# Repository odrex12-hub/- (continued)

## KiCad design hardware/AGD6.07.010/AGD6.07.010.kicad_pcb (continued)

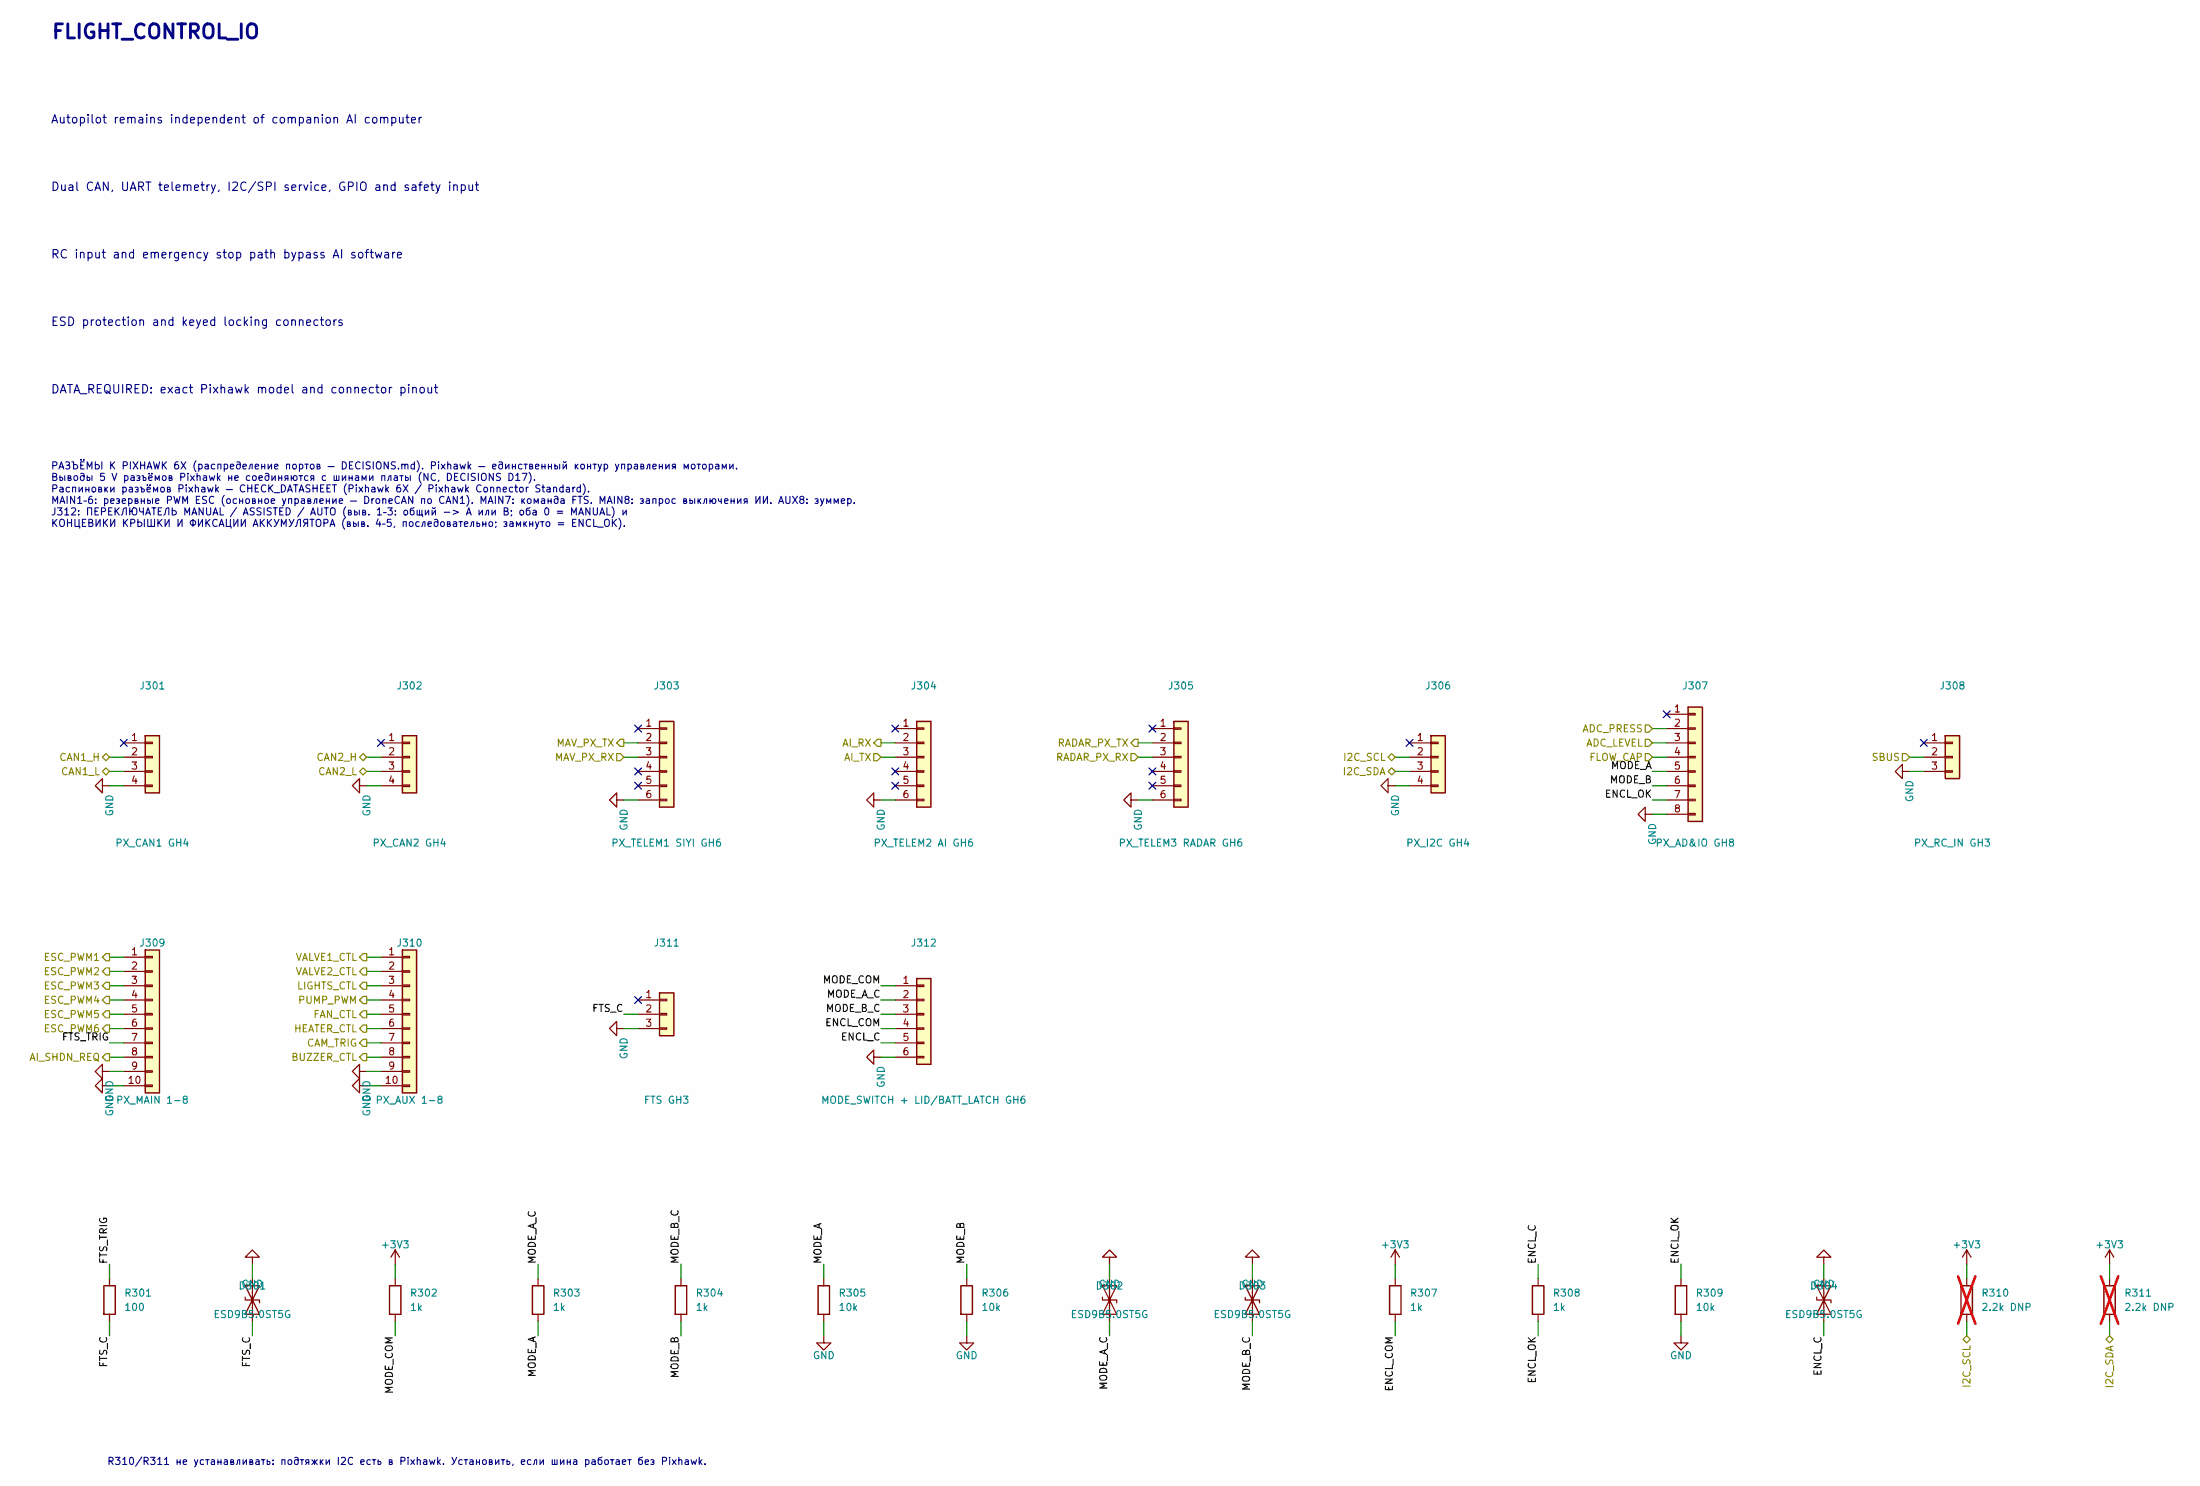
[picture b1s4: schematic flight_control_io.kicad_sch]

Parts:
D301, D302, D303, D304: ESD9B5.0ST5G; D_SOD-923
J301: PX_CAN1 GH4; JST_GH_SM04B-GHS-TB_1x04-1MP_P1.25mm_Horizontal
J302: PX_CAN2 GH4; JST_GH_SM04B-GHS-TB_1x04-1MP_P1.25mm_Horizontal
J303: PX_TELEM1 SIYI GH6; JST_GH_SM06B-GHS-TB_1x06-1MP_P1.25mm_Horizontal
J304: PX_TELEM2 AI GH6; JST_GH_SM06B-GHS-TB_1x06-1MP_P1.25mm_Horizontal
J305: PX_TELEM3 RADAR GH6; JST_GH_SM06B-GHS-TB_1x06-1MP_P1.25mm_Horizontal
J306: PX_I2C GH4; JST_GH_SM04B-GHS-TB_1x04-1MP_P1.25mm_Horizontal
J307: PX_AD&IO GH8; JST_GH_SM08B-GHS-TB_1x08-1MP_P1.25mm_Horizontal
J308: PX_RC_IN GH3; JST_GH_SM03B-GHS-TB_1x03-1MP_P1.25mm_Horizontal
J309: PX_MAIN 1-8; PinHeader_1x10_P2.54mm_Vertical
J310: PX_AUX 1-8; PinHeader_1x10_P2.54mm_Vertical
J311: FTS GH3; JST_GH_SM03B-GHS-TB_1x03-1MP_P1.25mm_Horizontal
J312: MODE_SWITCH + LID/BATT_LATCH GH6; JST_GH_SM06B-GHS-TB_1x06-1MP_P1.25mm_Horizontal
R301: 100; R_0402_1005Metric
R302, R303, R304, R307, R308: 1k; R_0402_1005Metric
R305, R306, R309: 10k; R_0402_1005Metric
R310, R311: 2.2k DNP; R_0402_1005Metric; not fitted

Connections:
+3V3: R302.1, R307.1, R310.1, R311.1; also elsewhere on the board
/ADC_LEVEL: J307.3; also elsewhere on the board
/ADC_PRESS: J307.2; also elsewhere on the board
/AI_RX: J304.2; also elsewhere on the board
/AI_SHDN_REQ: J309.8; also elsewhere on the board
/AI_TX: J304.3; also elsewhere on the board
/BUZZER_CTL: J310.8; also elsewhere on the board
/CAM_TRIG: J310.7; also elsewhere on the board
/CAN1_H: J301.2; also elsewhere on the board
/CAN1_L: J301.3; also elsewhere on the board
/CAN2_H: J302.2; also elsewhere on the board
/CAN2_L: J302.3; also elsewhere on the board
/ESC_PWM1: J309.1; also elsewhere on the board
/ESC_PWM2: J309.2; also elsewhere on the board
/ESC_PWM3: J309.3; also elsewhere on the board
/ESC_PWM4: J309.4; also elsewhere on the board
/ESC_PWM5: J309.5; also elsewhere on the board
/ESC_PWM6: J309.6; also elsewhere on the board
/FAN_CTL: J310.5; also elsewhere on the board
/FLIGHT_CONTROL_IO/ENCL_C: D304.1 (A1), J312.5, R308.1
/FLIGHT_CONTROL_IO/ENCL_COM: J312.4, R307.2
/FLIGHT_CONTROL_IO/ENCL_OK: J307.7, R308.2, R309.1
/FLIGHT_CONTROL_IO/FTS_C: D301.1 (A1), J311.2, R301.2
/FLIGHT_CONTROL_IO/FTS_TRIG: J309.7, R301.1
/FLIGHT_CONTROL_IO/MODE_A: J307.5, R303.2, R305.1
/FLIGHT_CONTROL_IO/MODE_A_C: D302.1 (A1), J312.2, R303.1
/FLIGHT_CONTROL_IO/MODE_B: J307.6, R304.2, R306.1
/FLIGHT_CONTROL_IO/MODE_B_C: D303.1 (A1), J312.3, R304.1
/FLIGHT_CONTROL_IO/MODE_COM: J312.1, R302.2
/FLOW_CAP: J307.4; also elsewhere on the board
/HEATER_CTL: J310.6; also elsewhere on the board
/I2C_SCL: J306.2, R310.2; also elsewhere on the board
/I2C_SDA: J306.3, R311.2; also elsewhere on the board
/LIGHTS_CTL: J310.3; also elsewhere on the board
/MAV_PX_RX: J303.3; also elsewhere on the board
/MAV_PX_TX: J303.2; also elsewhere on the board
/PUMP_PWM: J310.4; also elsewhere on the board
/RADAR_PX_RX: J305.3; also elsewhere on the board
/RADAR_PX_TX: J305.2; also elsewhere on the board
/SBUS: J308.2; also elsewhere on the board
/VALVE1_CTL: J310.1; also elsewhere on the board
/VALVE2_CTL: J310.2; also elsewhere on the board
GND: D301.2 (A2), D302.2 (A2), D303.2 (A2), D304.2 (A2), J301.4, J302.4, J303.6, J304.6, J305.6, J306.4, J307.8, J308.3, J309.9, J309.10, J310.9, J310.10, J311.3, J312.6, R305.2, R306.2, R309.2; also elsewhere on the board

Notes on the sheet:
RC input and emergency stop path bypass AI software
Dual CAN, UART telemetry, I2C/SPI service, GPIO and safety input
Autopilot remains independent of companion AI computer
FLIGHT_CONTROL_IO
DATA_REQUIRED: exact Pixhawk model and connector pinout
ESD protection and keyed locking connectors
РАЗЪЁМЫ К PIXHAWK 6X (распределение портов — DECISIONS.md). Pixhawk — единственный контур управления моторами. Выводы 5 V разъёмов Pixhawk не соединяются с шинами платы (NC, DECISIONS D17). Распиновки разъёмов Pixhawk — CHECK_DATASHEET (Pixhawk 6X / Pixhawk Connector Standard). MAIN1–6: резервные P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
R310/R311 не устанавливать: подтяжки I2C есть в Pixhawk. Установить, если шина работает без Pixhawk.

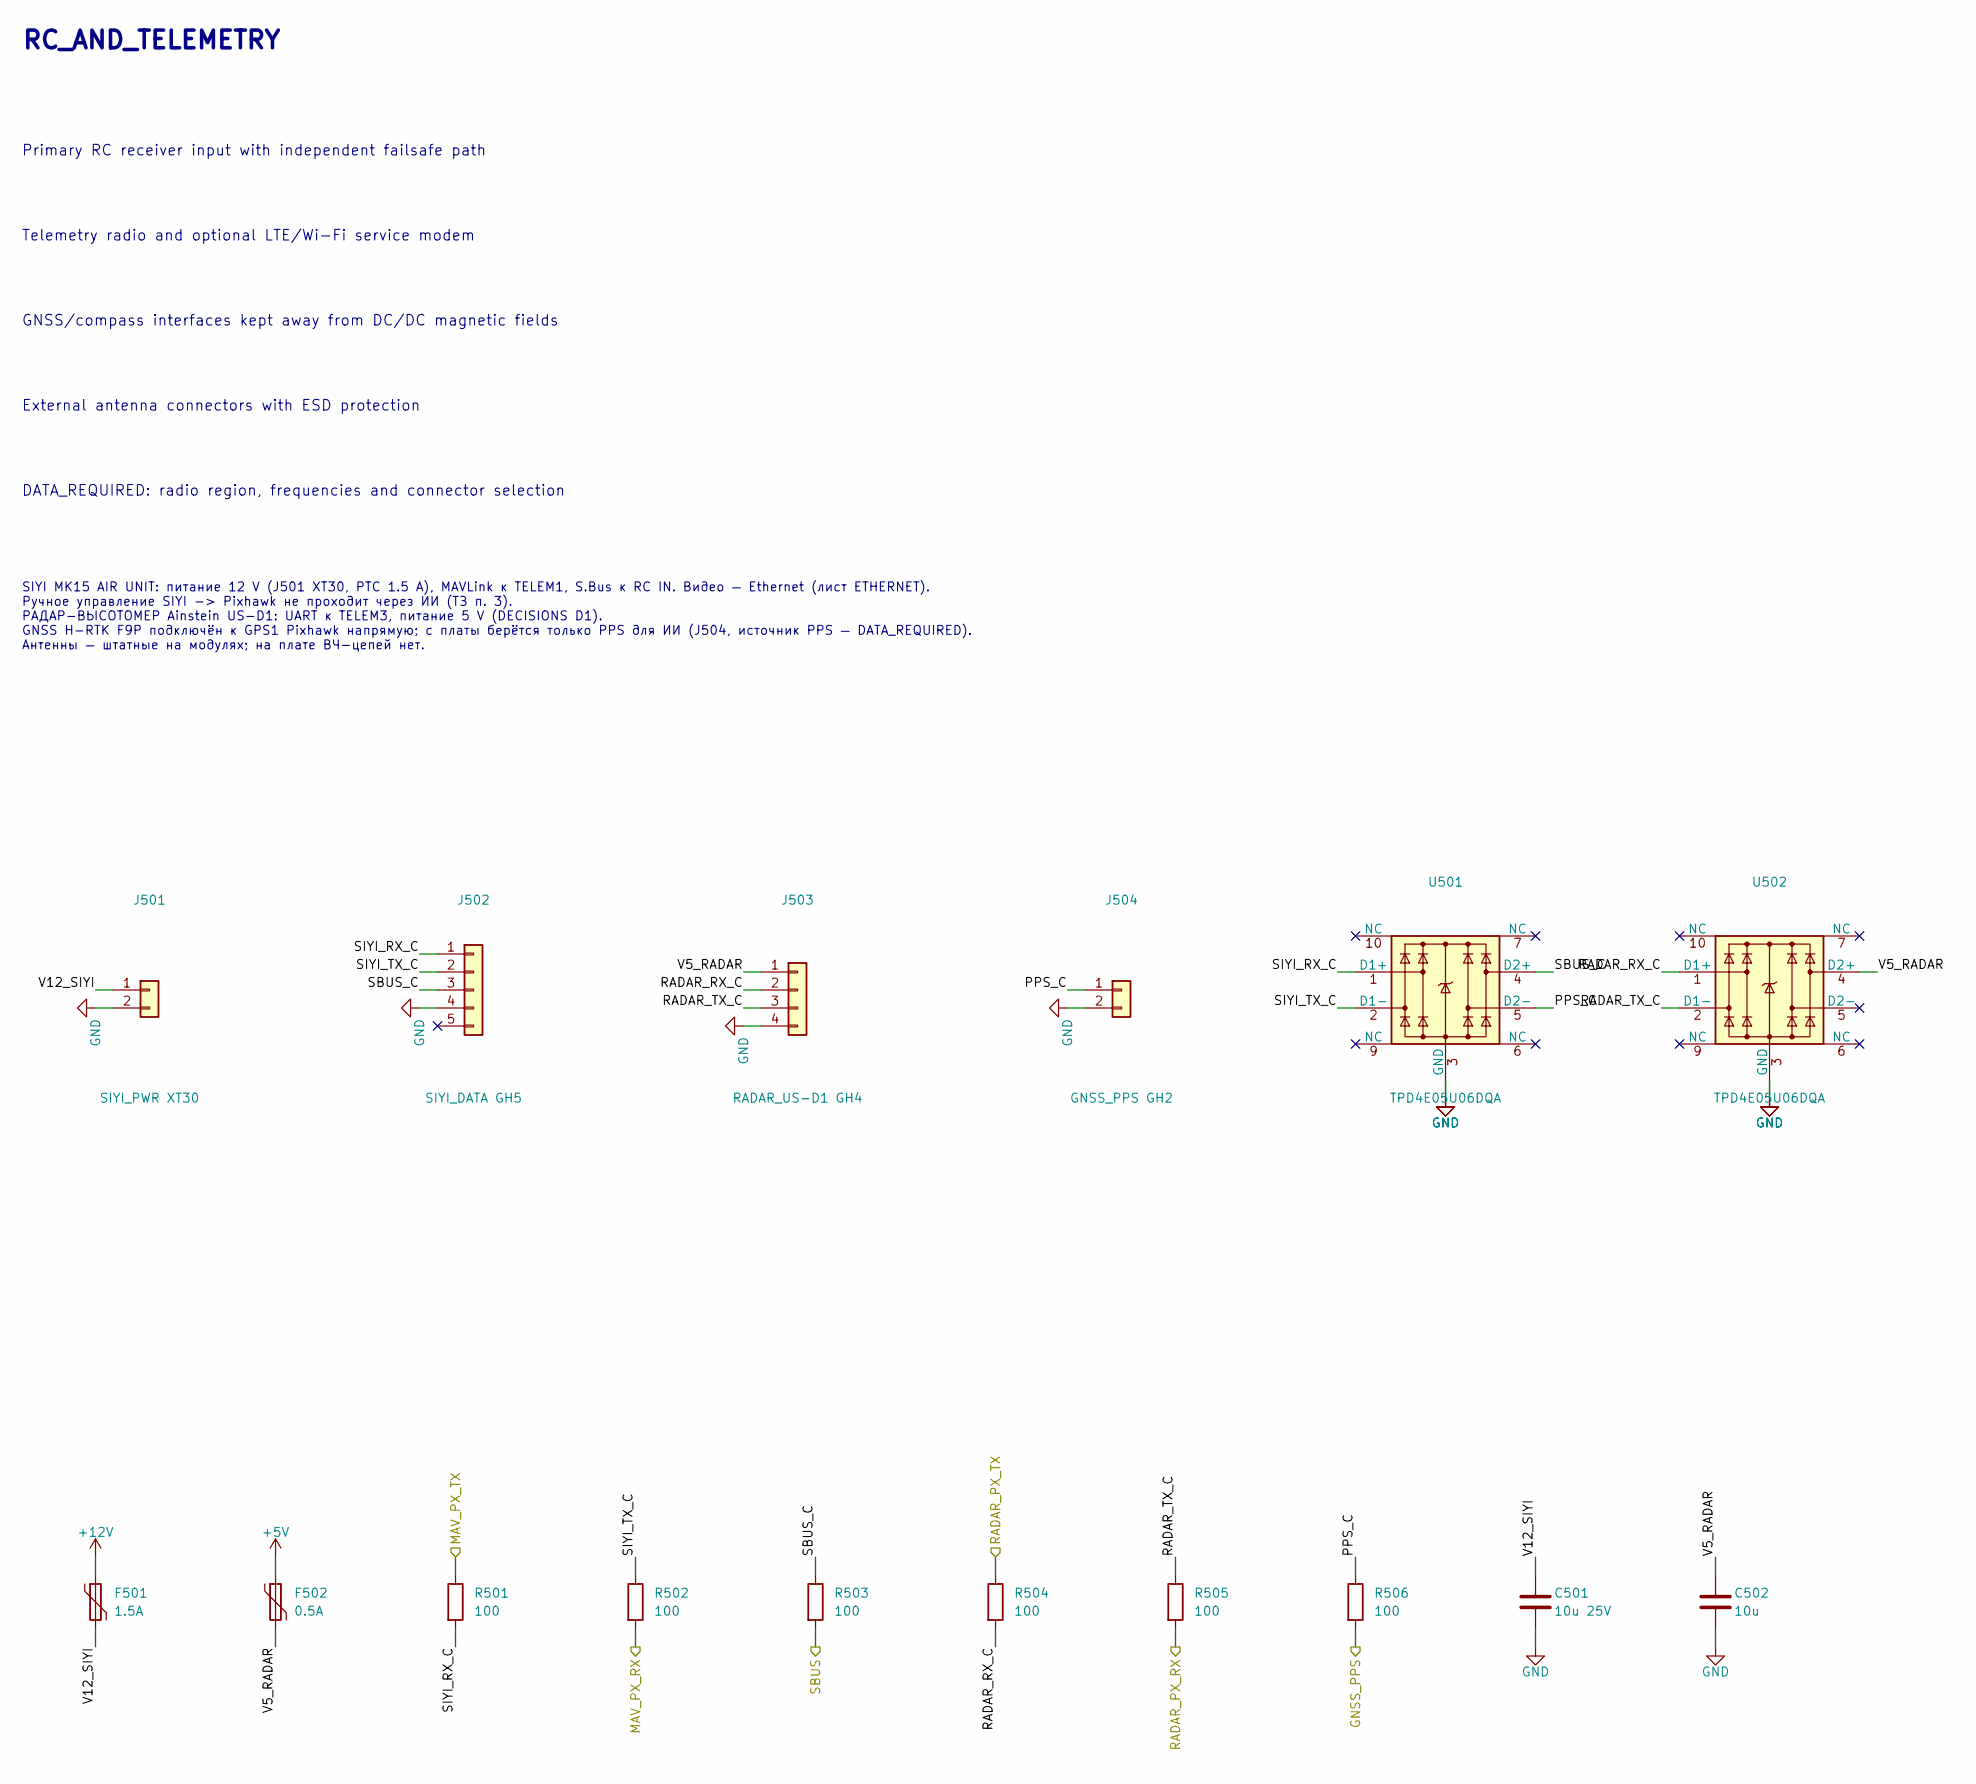
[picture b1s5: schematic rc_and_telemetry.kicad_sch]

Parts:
C501: 10u 25V; C_1210_3225Metric
C502: 10u; C_0805_2012Metric
F501: 1.5A; Fuse_1812_4532Metric
F502: 0.5A; Fuse_1206_3216Metric
J501: SIYI_PWR XT30; AMASS_XT30PW-F_1x02_P2.50mm_Horizontal
J502: SIYI_DATA GH5; JST_GH_SM05B-GHS-TB_1x05-1MP_P1.25mm_Horizontal
J503: RADAR_US-D1 GH4; JST_GH_SM04B-GHS-TB_1x04-1MP_P1.25mm_Horizontal
J504: GNSS_PPS GH2; JST_GH_SM02B-GHS-TB_1x02-1MP_P1.25mm_Horizontal
R501, R502, R503, R504, R505, R506: 100; R_0402_1005Metric
U501, U502: TPD4E05U06DQA; USON-10_2.5x1.0mm_P0.5mm

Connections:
+5V: F502.1; also elsewhere on the board
+12V: F501.1; also elsewhere on the board
/GNSS_PPS: R506.2; also elsewhere on the board
/MAV_PX_RX: R502.2; also elsewhere on the board
/MAV_PX_TX: R501.1; also elsewhere on the board
/RADAR_PX_RX: R505.2; also elsewhere on the board
/RADAR_PX_TX: R504.1; also elsewhere on the board
/RC_AND_TELEMETRY/PPS_C: J504.1, R506.1, U501.5 (D2-)
/RC_AND_TELEMETRY/RADAR_RX_C: J503.2, R504.2, U502.1 (D1+)
/RC_AND_TELEMETRY/RADAR_TX_C: J503.3, R505.1, U502.2 (D1-)
/RC_AND_TELEMETRY/SBUS_C: J502.3, R503.1, U501.4 (D2+)
/RC_AND_TELEMETRY/SIYI_RX_C: J502.1, R501.2, U501.1 (D1+)
/RC_AND_TELEMETRY/SIYI_TX_C: J502.2, R502.1, U501.2 (D1-)
/RC_AND_TELEMETRY/V5_RADAR: C502.1, F502.2, J503.1, U502.4 (D2+)
/RC_AND_TELEMETRY/V12_SIYI: C501.1, F501.2, J501.1
/SBUS: R503.2; also elsewhere on the board
GND: C501.2, C502.2, J501.2, J502.4, J503.4, J504.2, U501.3 (GND), U501.8 (GND), U502.3 (GND), U502.8 (GND); also elsewhere on the board

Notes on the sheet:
DATA_REQUIRED: radio region, frequencies and connector selection
Primary RC receiver input with independent failsafe path
GNSS/compass interfaces kept away from DC/DC magnetic fields
Telemetry radio and optional LTE/Wi-Fi service modem
RC_AND_TELEMETRY
External antenna connectors with ESD protection
SIYI MK15 AIR UNIT: питание 12 V (J501 XT30, PTC 1.5 A), MAVLink к TELEM1, S.Bus к RC IN. Видео — Ethernet (лист ETHERNET). Ручное управление SIYI -> Pixhawk не проходит через ИИ (ТЗ п. 3). РАДАР-ВЫСОТОМЕР Ainstein US-D1: UART к TELEM3, питание 5 V (DECISIONS D1). GNSS H-RTK F9P подключён к GPS1 Pi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

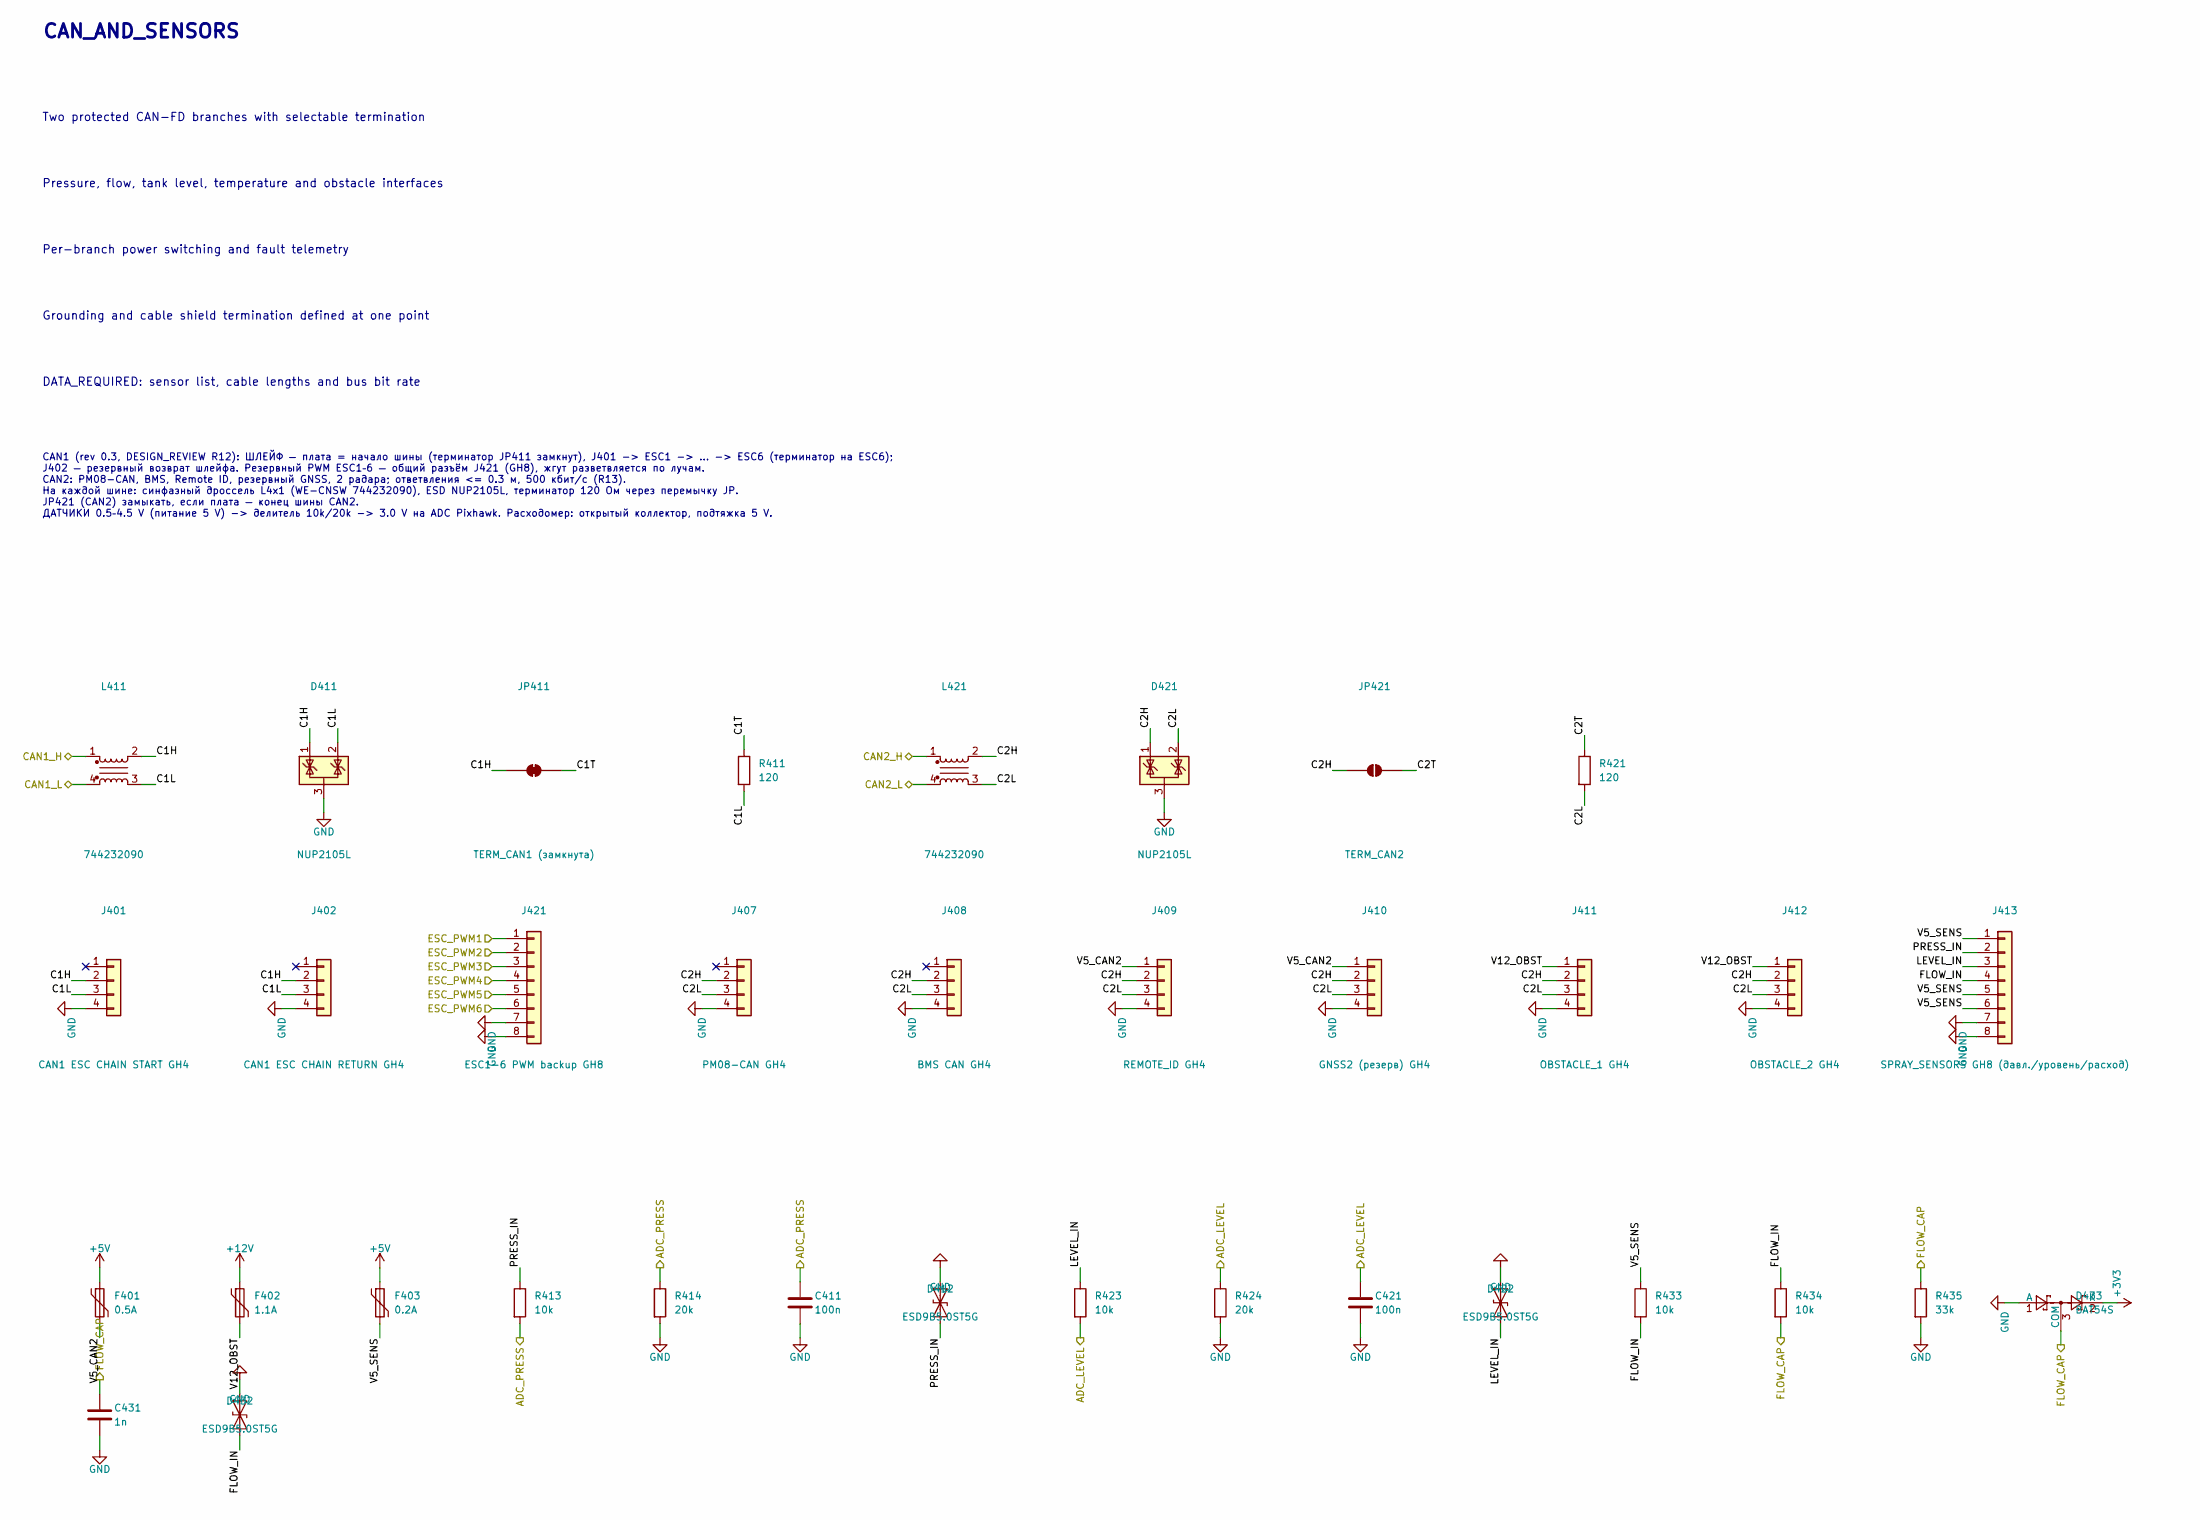
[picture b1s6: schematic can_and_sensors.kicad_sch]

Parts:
C411, C421: 100n; C_0402_1005Metric
C431: 1n; C_0402_1005Metric
D411, D421: NUP2105L; SOT-23
D412, D422, D432: ESD9B5.0ST5G; D_SOD-923
D433: BAT54S; SOT-23
F401: 0.5A; Fuse_1206_3216Metric
F402: 1.1A; Fuse_1812_4532Metric
F403: 0.2A; Fuse_1206_3216Metric
J401: CAN1 ESC CHAIN START GH4; JST_GH_SM04B-GHS-TB_1x04-1MP_P1.25mm_Horizontal
J402: CAN1 ESC CHAIN RETURN GH4; JST_GH_SM04B-GHS-TB_1x04-1MP_P1.25mm_Horizontal
J407: PM08-CAN GH4; JST_GH_SM04B-GHS-TB_1x04-1MP_P1.25mm_Horizontal
J408: BMS CAN GH4; JST_GH_SM04B-GHS-TB_1x04-1MP_P1.25mm_Horizontal
J409: REMOTE_ID GH4; JST_GH_SM04B-GHS-TB_1x04-1MP_P1.25mm_Horizontal
J410: GNSS2 (резерв) GH4; JST_GH_SM04B-GHS-TB_1x04-1MP_P1.25mm_Horizontal
J411: OBSTACLE_1 GH4; JST_GH_SM04B-GHS-TB_1x04-1MP_P1.25mm_Horizontal
J412: OBSTACLE_2 GH4; JST_GH_SM04B-GHS-TB_1x04-1MP_P1.25mm_Horizontal
J413: SPRAY_SENSORS GH8 (давл./уровень/расход); JST_GH_SM08B-GHS-TB_1x08-1MP_P1.25mm_Horizontal
J421: ESC1-6 PWM backup GH8; JST_GH_SM08B-GHS-TB_1x08-1MP_P1.25mm_Horizontal
JP411: TERM_CAN1 (замкнута); SolderJumper-2_P1.3mm_Bridged_RoundedPad1.0x1.5mm
JP421: TERM_CAN2; SolderJumper-2_P1.3mm_Open_RoundedPad1.0x1.5mm
L411, L421: 744232090; L_CommonMode_Wurth_WE-CNSW-1206
R411, R421: 120; R_0805_2012Metric
R413, R423, R433, R434: 10k; R_0402_1005Metric
R414, R424: 20k; R_0402_1005Metric
R435: 33k; R_0402_1005Metric

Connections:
+3V3: D433.2 (K); also elsewhere on the board
+5V: F401.1, F403.1; also elsewhere on the board
+12V: F402.1; also elsewhere on the board
/ADC_LEVEL: C421.1, R423.2, R424.1; also elsewhere on the board
/ADC_PRESS: C411.1, R413.2, R414.1; also elsewhere on the board
/CAN1_H: L411.1; also elsewhere on the board
/CAN1_L: L411.4; also elsewhere on the board
/CAN2_H: L421.1; also elsewhere on the board
/CAN2_L: L421.4; also elsewhere on the board
/CAN_AND_SENSORS/C1H: D411.1 (K), J401.2, J402.2, JP411.1 (A), L411.2
/CAN_AND_SENSORS/C1L: D411.2 (K), J401.3, J402.3, L411.3, R411.2
/CAN_AND_SENSORS/C1T: JP411.2 (B), R411.1
/CAN_AND_SENSORS/C2H: D421.1 (K), J407.2, J408.2, J409.2, J410.2, J411.2, J412.2, JP421.1 (A), L421.2
/CAN_AND_SENSORS/C2L: D421.2 (K), J407.3, J408.3, J409.3, J410.3, J411.3, J412.3, L421.3, R421.2
/CAN_AND_SENSORS/C2T: JP421.2 (B), R421.1
/CAN_AND_SENSORS/FLOW_IN: D432.1 (A1), J413.4, R433.2, R434.1
/CAN_AND_SENSORS/LEVEL_IN: D422.1 (A1), J413.3, R423.1
/CAN_AND_SENSORS/PRESS_IN: D412.1 (A1), J413.2, R413.1
/CAN_AND_SENSORS/V5_CAN2: F401.2, J409.1, J410.1
/CAN_AND_SENSORS/V5_SENS: F403.2, J413.1, J413.5, J413.6, R433.1
/CAN_AND_SENSORS/V12_OBST: F402.2, J411.1, J412.1
/ESC_PWM1: J421.1; also elsewhere on the board
/ESC_PWM2: J421.2; also elsewhere on the board
/ESC_PWM3: J421.3; also elsewhere on the board
/ESC_PWM4: J421.4; also elsewhere on the board
/ESC_PWM5: J421.5; also elsewhere on the board
/ESC_PWM6: J421.6; also elsewhere on the board
/FLOW_CAP: C431.1, D433.3 (COM), R434.2, R435.1; also elsewhere on the board
GND: C411.2, C421.2, C431.2, D411.3 (A), D412.2 (A2), D421.3 (A), D422.2 (A2), D432.2 (A2), D433.1 (A), J401.4, J402.4, J407.4, J408.4, J409.4, J410.4, J411.4, J412.4, J413.7, J413.8, J421.7, J421.8, R414.2, R424.2, R435.2; also elsewhere on the board

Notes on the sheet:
Grounding and cable shield termination defined at one point
Two protected CAN-FD branches with selectable termination
DATA_REQUIRED: sensor list, cable lengths and bus bit rate
Pressure, flow, tank level, temperature and obstacle interfaces
Per-branch power switching and fault telemetry
CAN_AND_SENSORS
CAN1 (rev 0.3, DESIGN_REVIEW R12): ШЛЕЙФ — плата = начало шины (терминатор JP411 замкнут), J401 -> ESC1 -> ... -> ESC6 (терминатор на ESC6); J402 — резервный возврат шлейфа. Резервный PWM ESC1–6 — общий разъём J421 (GH8), жгут разветвляется по лучам. CAN2: PM08-CAN, BMS, Remote ID, резервный GNSS, 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

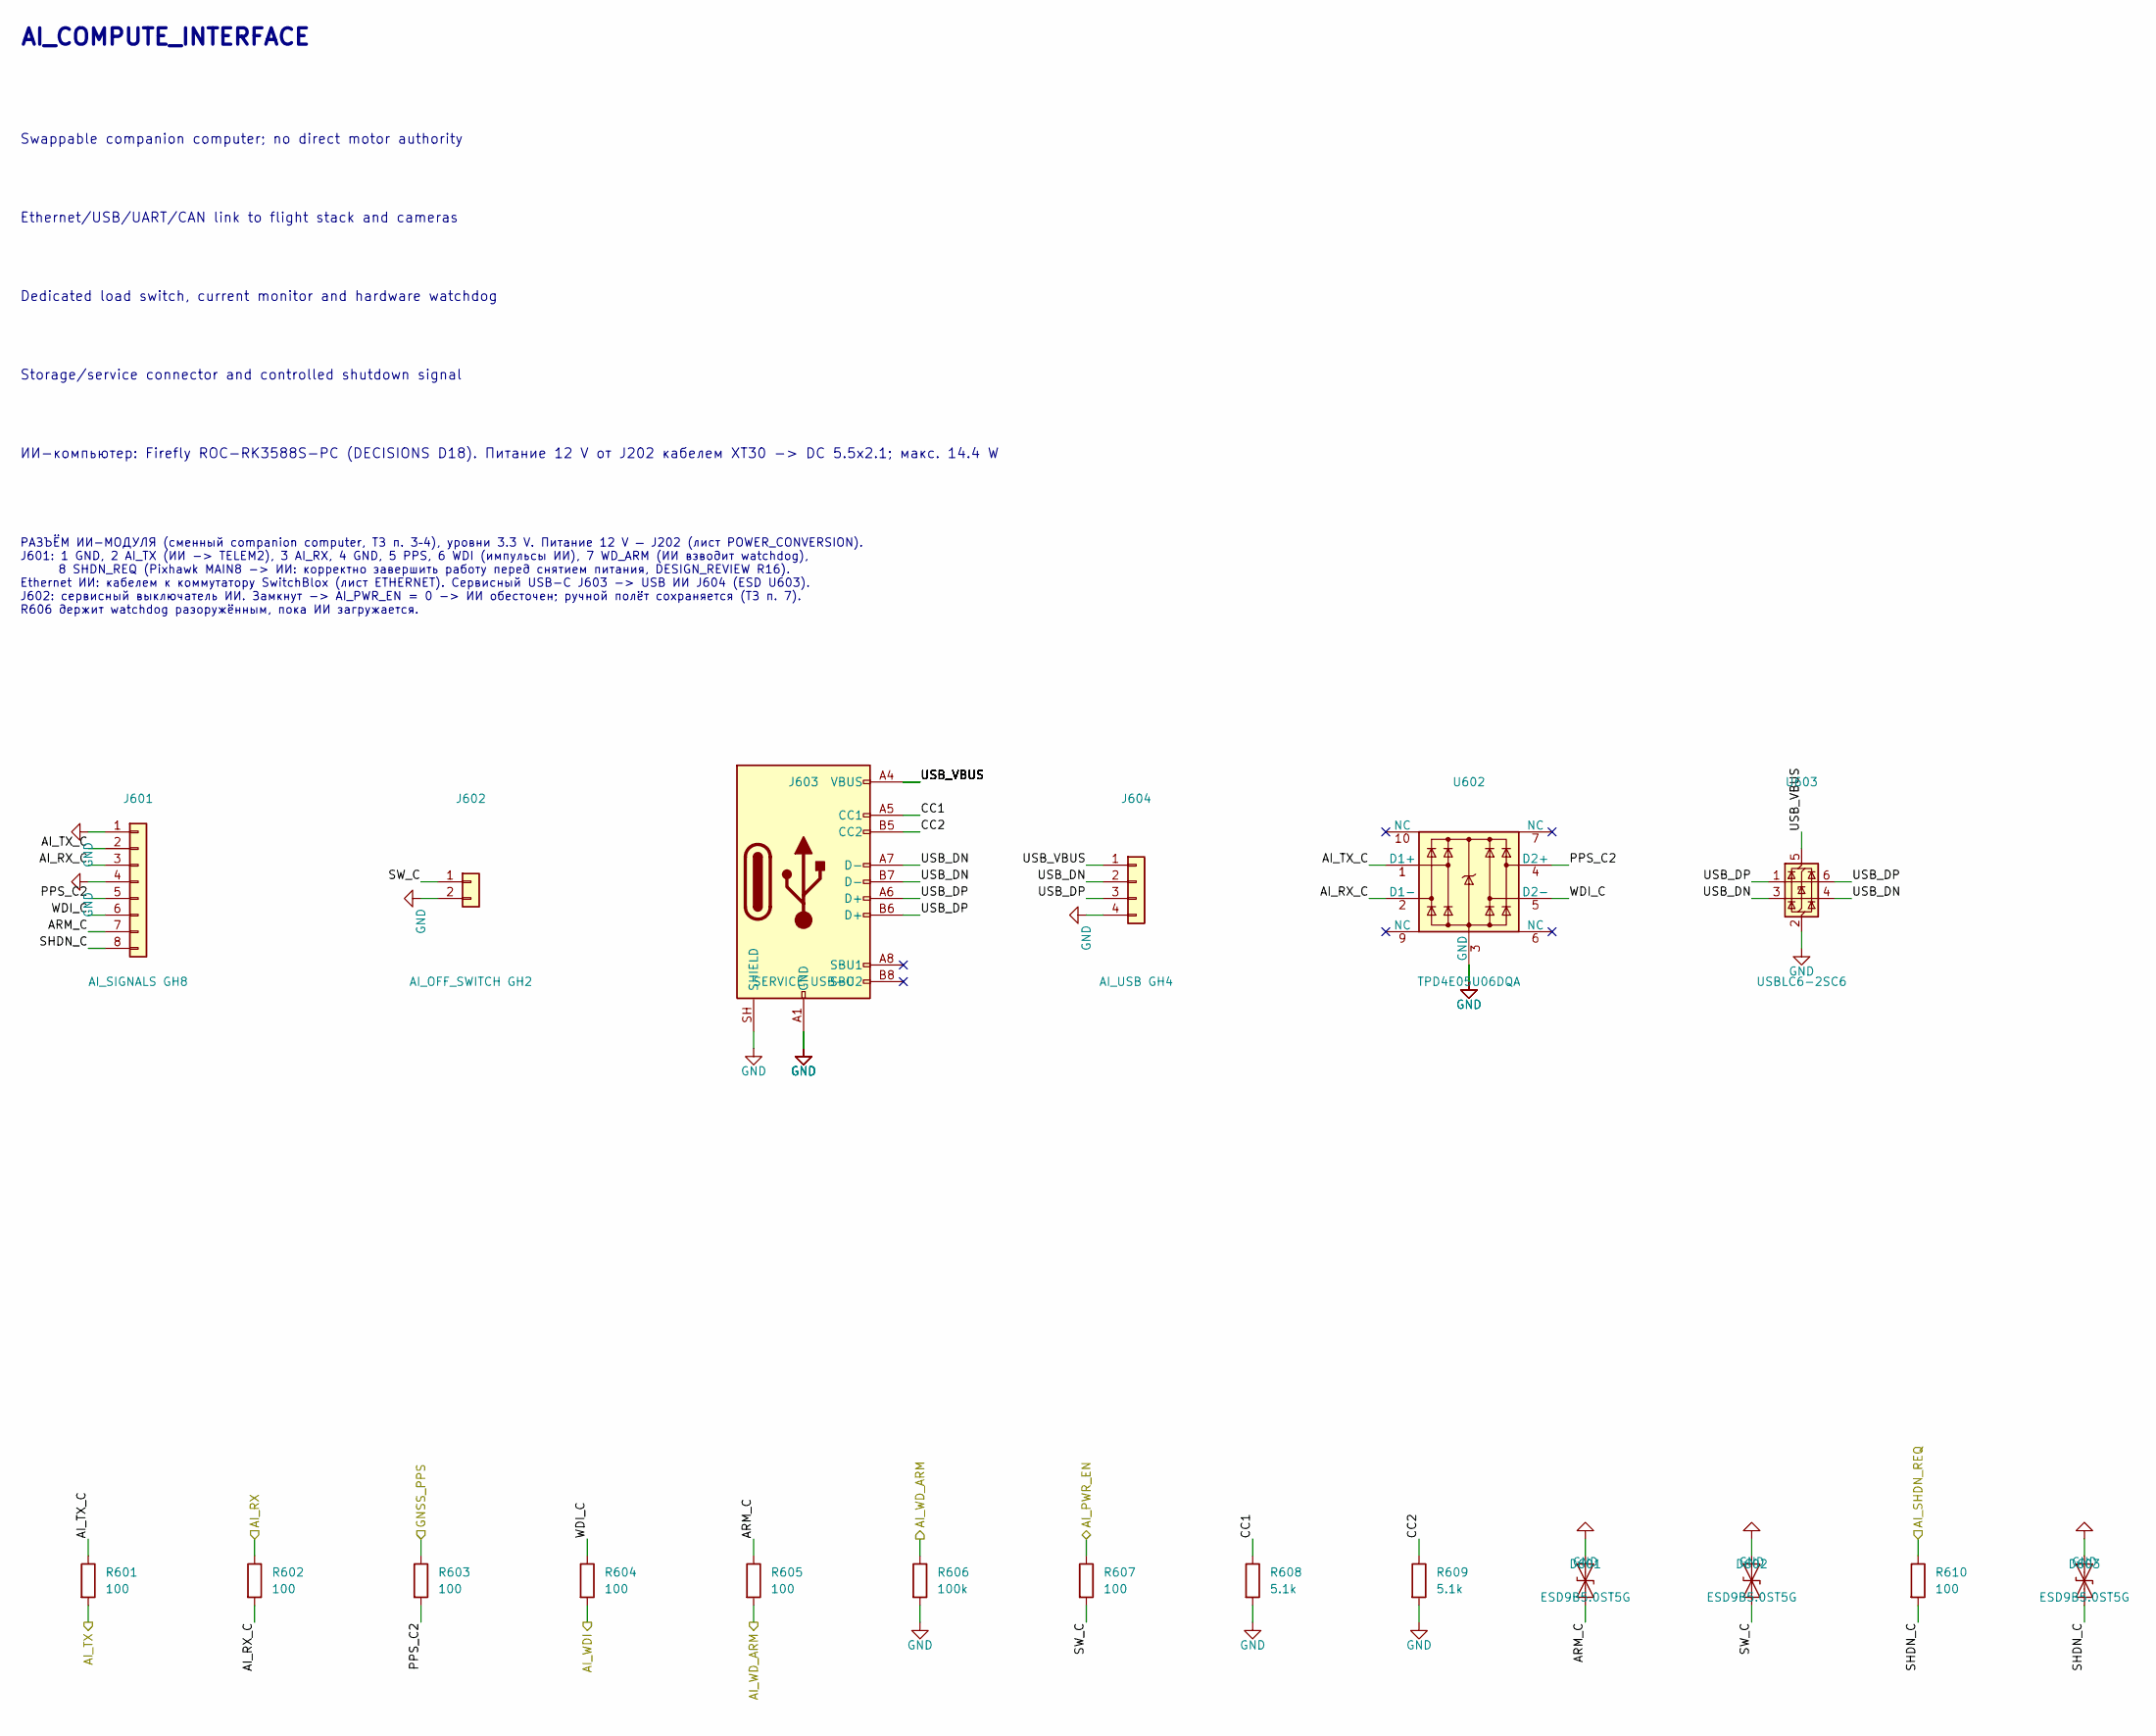
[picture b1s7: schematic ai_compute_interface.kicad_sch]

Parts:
D601, D602, D603: ESD9B5.0ST5G; D_SOD-923
J601: AI_SIGNALS GH8; JST_GH_SM08B-GHS-TB_1x08-1MP_P1.25mm_Horizontal
J602: AI_OFF_SWITCH GH2; JST_GH_SM02B-GHS-TB_1x02-1MP_P1.25mm_Horizontal
J603: SERVICE USB-C; USB_C_Receptacle_GCT_USB4105-xx-A_16P_TopMnt_Horizontal
J604: AI_USB GH4; JST_GH_SM04B-GHS-TB_1x04-1MP_P1.25mm_Horizontal
R601, R602, R603, R604, R605, R607, R610: 100; R_0402_1005Metric
R606: 100k; R_0402_1005Metric
R608, R609: 5.1k; R_0402_1005Metric
U602: TPD4E05U06DQA; USON-10_2.5x1.0mm_P0.5mm
U603: USBLC6-2SC6; SOT-23-6

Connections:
/AI_COMPUTE_INTERFACE/AI_RX_C: J601.3, R602.2, U602.2 (D1-)
/AI_COMPUTE_INTERFACE/AI_TX_C: J601.2, R601.1, U602.1 (D1+)
/AI_COMPUTE_INTERFACE/ARM_C: D601.1 (A1), J601.7, R605.1
/AI_COMPUTE_INTERFACE/CC1: J603.A5 (CC1), R608.1
/AI_COMPUTE_INTERFACE/CC2: J603.B5 (CC2), R609.1
/AI_COMPUTE_INTERFACE/PPS_C2: J601.5, R603.2, U602.4 (D2+)
/AI_COMPUTE_INTERFACE/SHDN_C: D603.1 (A1), J601.8, R610.2
/AI_COMPUTE_INTERFACE/SW_C: D602.1 (A1), J602.1, R607.2
/AI_COMPUTE_INTERFACE/USB_DN: J603.A7 (D-), J603.B7 (D-), J604.2, U603.3 (I/O2), U603.4 (I/O2)
/AI_COMPUTE_INTERFACE/USB_DP: J603.A6 (D+), J603.B6 (D+), J604.3, U603.1 (I/O1), U603.6 (I/O1)
/AI_COMPUTE_INTERFACE/USB_VBUS: J603.A4 (VBUS), J603.A9 (VBUS), J603.B4 (VBUS), J603.B9 (VBUS), J604.1, U603.5 (VBUS)
/AI_COMPUTE_INTERFACE/WDI_C: J601.6, R604.1, U602.5 (D2-)
/AI_PWR_EN: R607.1; also elsewhere on the board
/AI_RX: R602.1; also elsewhere on the board
/AI_SHDN_REQ: R610.1; also elsewhere on the board
/AI_TX: R601.2; also elsewhere on the board
/AI_WDI: R604.2; also elsewhere on the board
/AI_WD_ARM: R605.2, R606.1; also elsewhere on the board
/GNSS_PPS: R603.1; also elsewhere on the board
GND: D601.2 (A2), D602.2 (A2), D603.2 (A2), J601.1, J601.4, J602.2, J603.A1 (GND), J603.A12 (GND), J603.B1 (GND), J603.B12 (GND), J603.SH (SHIELD), J604.4, R606.2, R608.2, R609.2, U602.3 (GND), U602.8 (GND), U603.2 (GND); also elsewhere on the board

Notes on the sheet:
Storage/service connector and controlled shutdown signal
ИИ-компьютер: Firefly ROC-RK3588S-PC (DECISIONS D18). Питание 12 V от J202 кабелем XT30 -> DC 5.5x2.1; макс. 14.4 W
AI_COMPUTE_INTERFACE
Ethernet/USB/UART/CAN link to flight stack and cameras
Swappable companion computer; no direct motor authority
Dedicated load switch, current monitor and hardware watchdog
РАЗЪЁМ ИИ-МОДУЛЯ (сменный companion computer, ТЗ п. 3–4), уровни 3.3 V. Питание 12 V — J202 (лист POWER_CONVERSION). J601: 1 GND, 2 AI_TX (ИИ -> TELEM2), 3 AI_RX, 4 GND, 5 PPS, 6 WDI (импульсы ИИ), 7 WD_ARM (ИИ взводит watchdog), 8 SHDN_REQ (Pixhawk MAIN8 -> ИИ: корректно завершить работу перед сня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
